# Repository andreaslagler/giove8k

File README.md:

# giove8k
Giove 8k audio synthesizer project

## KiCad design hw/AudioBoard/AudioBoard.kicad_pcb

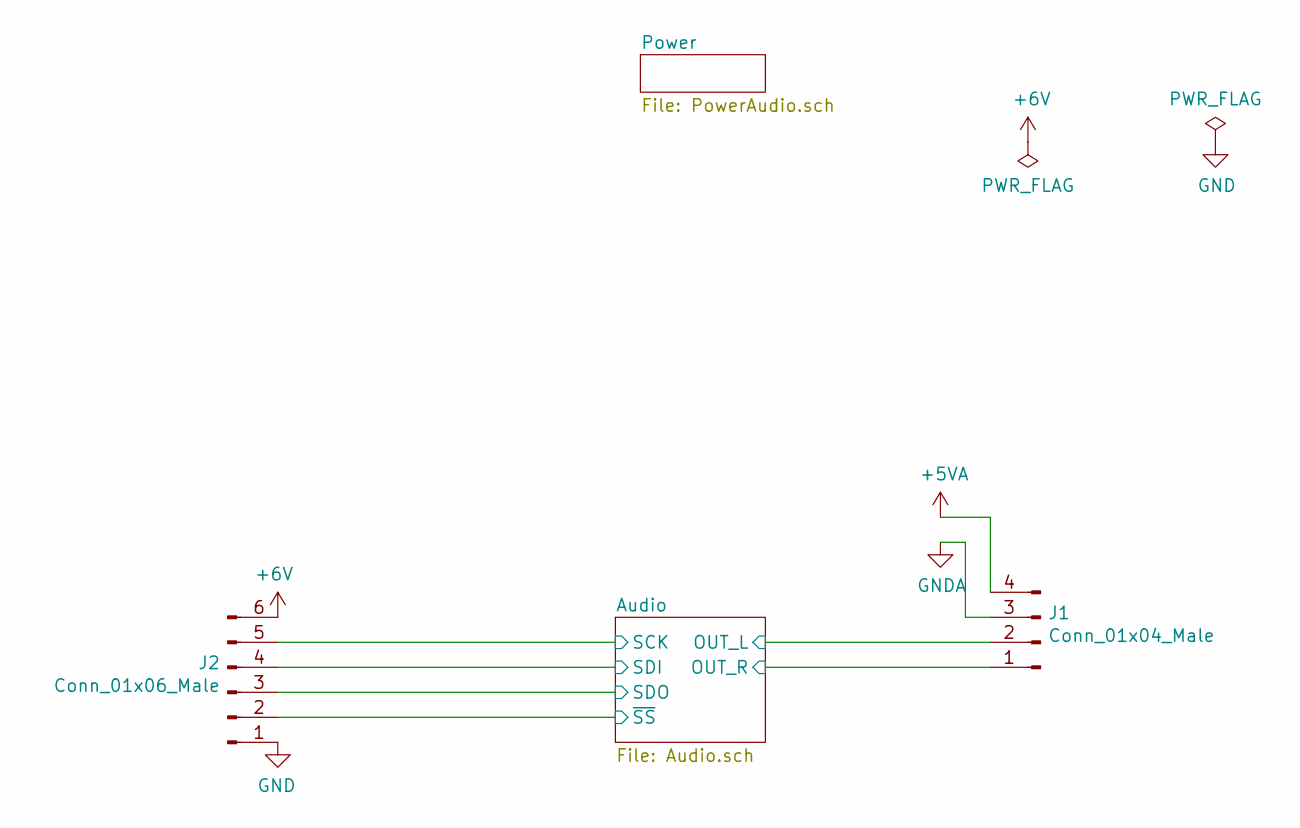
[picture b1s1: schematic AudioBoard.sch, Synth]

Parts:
J1: Conn_01x04_Male; PinHeader_1x04_P2.54mm_Vertical
J2: Conn_01x06_Male; PinHeader_1x06_P2.54mm_Vertical

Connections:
+5VA: J1.4; also elsewhere on the board
+6V: J2.6; also elsewhere on the board
/Audio/OUT_L: J1.2; also elsewhere on the board
/Audio/OUT_R: J1.1; also elsewhere on the board
/Audio/SCK: J2.5; also elsewhere on the board
/Audio/SDI: J2.4; also elsewhere on the board
/Audio/SDO: J2.3; also elsewhere on the board
/Audio/~SS: J2.2; also elsewhere on the board
GND: J1.3, J2.1; also elsewhere on the board

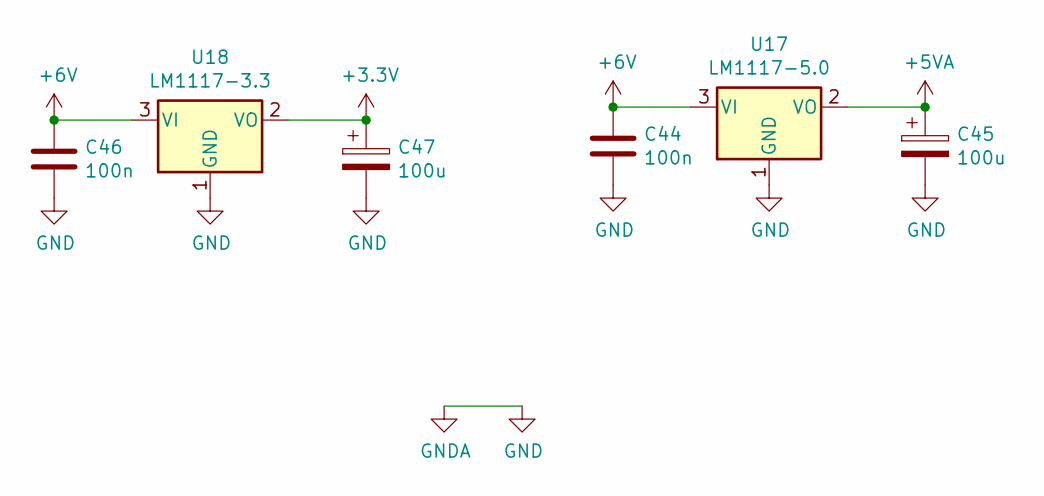
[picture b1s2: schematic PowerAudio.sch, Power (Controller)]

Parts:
C44, C46: 100n; C_Disc_D4.3mm_W1.9mm_P5.00mm
C45, C47: 100u; CP_Radial_D8.0mm_P5.00mm
U17: LM1117-5.0; TO-220F-3_Horizontal_TabDown
U18: LM1117-3.3; TO-220F-3_Horizontal_TabDown

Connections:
+3V3: C47.1, U18.2 (VO); also elsewhere on the board
+5VA: C45.1, U17.2 (VO); also elsewhere on the board
+6V: C44.1, C46.1, U17.3 (VI), U18.3 (VI); also elsewhere on the board
GND: C44.2, C45.2, C46.2, C47.2, U17.1 (GND), U18.1 (GND); also elsewhere on the board

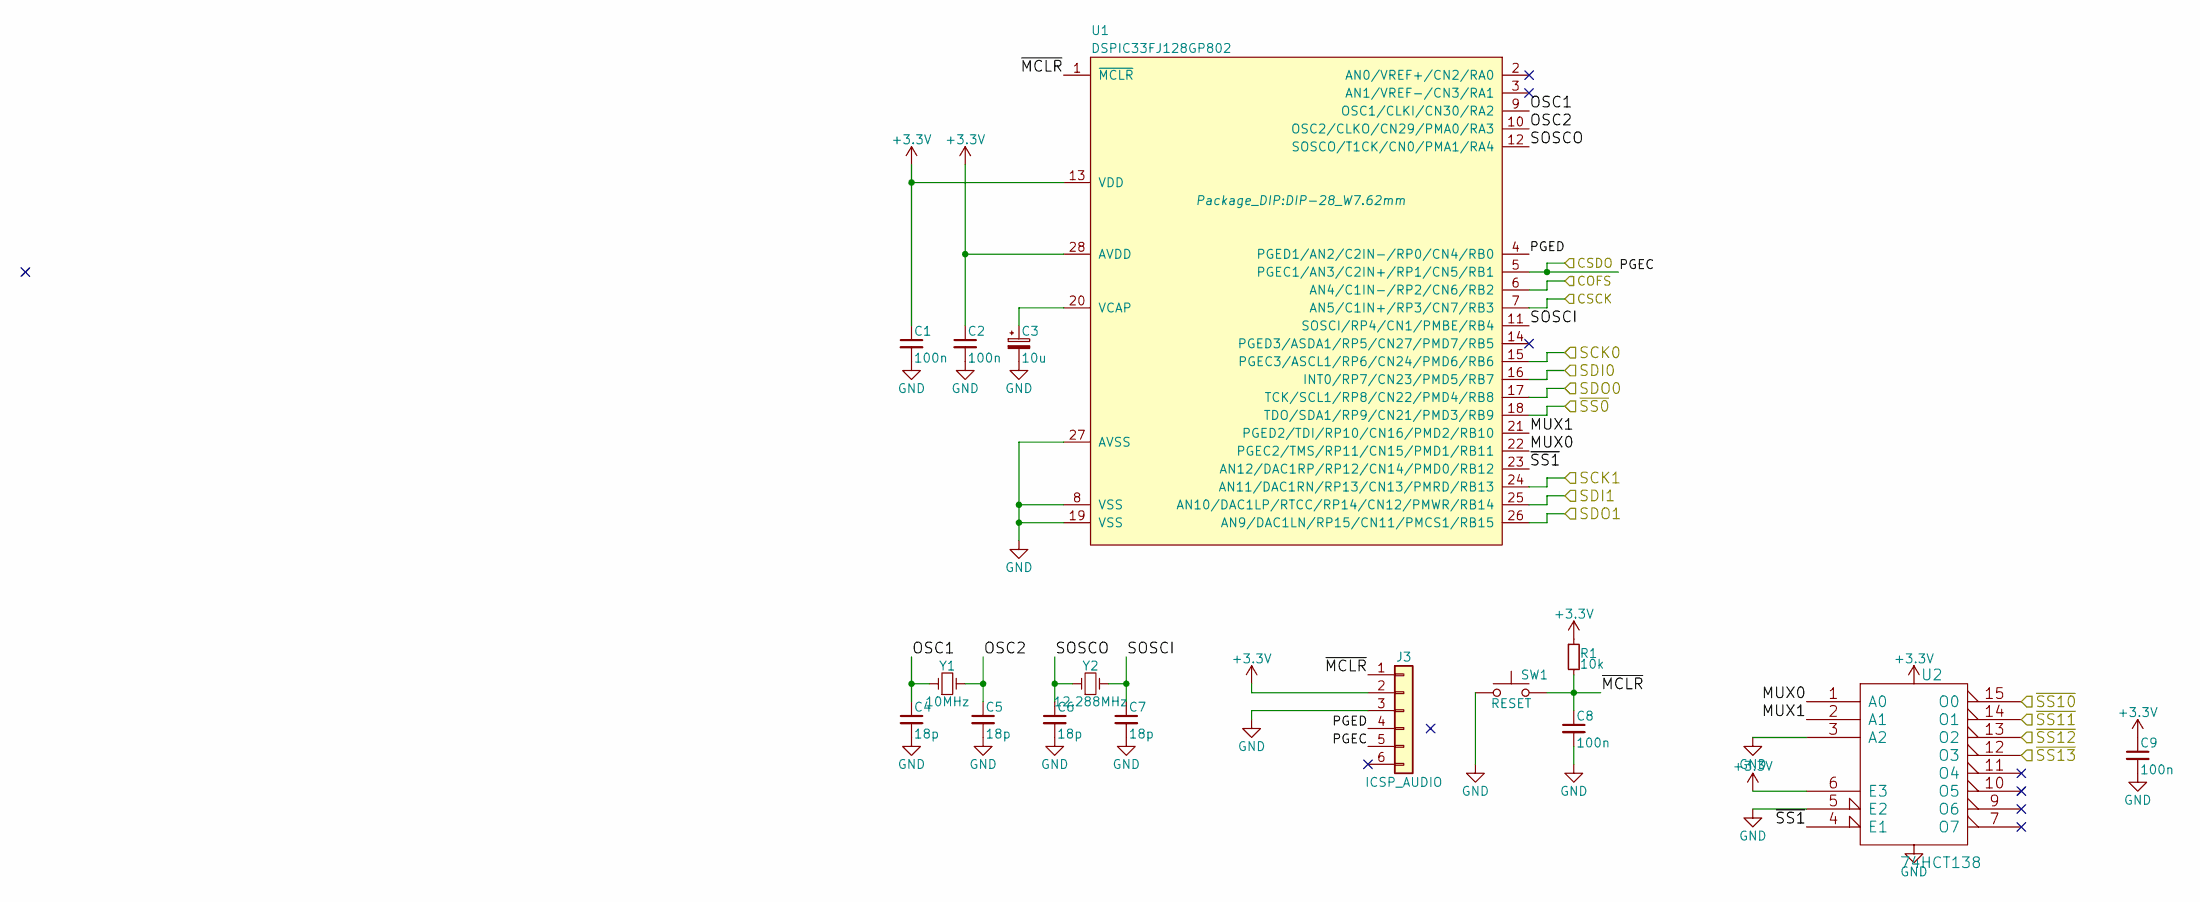
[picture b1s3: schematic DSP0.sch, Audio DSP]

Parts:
C1, C2, C8, C9: 100n; C_Disc_D4.3mm_W1.9mm_P5.00mm
C3: 10u; CP_Radial_D5.0mm_P2.50mm
C4, C5, C6, C7: 18p; C_Disc_D3.0mm_W1.6mm_P2.50mm
J3: ICSP_AUDIO; Molex_KK-254_AE-6410-06A_1x06_P2.54mm_Vertical
R1: 10k; R_Axial_DIN0207_L6.3mm_D2.5mm_P10.16mm_Horizontal
SW1: RESET; SW_PUSH_6mm
U1: DSPIC33FJ128GP802; DIP-28_W7.62mm
U2: 74HCT138; DIP-16_W7.62mm
Y1: 10MHz; Crystal_HC49-U_Vertical
Y2: 12.288MHz; Crystal_HC49-U_Vertical

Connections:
+3V3: C1.1, C2.1, C9.1, J3.2, R1.1, U1.13 (VDD), U1.28 (AVDD), U2.6 (E3), U2.16 (VCC); also elsewhere on the board
/Audio/COFS: U1.6 (AN4/C1IN-/RP2/CN6/RB2); also elsewhere on the board
/Audio/CSDO: J3.5, U1.5 (PGEC1/AN3/C2IN+/RP1/CN5/RB1); also elsewhere on the board
/Audio/CSK: U1.7 (AN5/C1IN+/RP3/CN7/RB3); also elsewhere on the board
/Audio/DSP0/MUX0: U1.22 (PGEC2/TMS/RP11/CN15/PMD1/RB11), U2.1 (A0)
/Audio/DSP0/MUX1: U1.21 (PGED2/TDI/RP10/CN16/PMD2/RB10), U2.2 (A1)
/Audio/DSP0/OSC1: C4.1, U1.9 (OSC1/CLKI/CN30/RA2), Y1.1
/Audio/DSP0/OSC2: C5.1, U1.10 (OSC2/CLKO/CN29/PMA0/RA3), Y1.2
/Audio/DSP0/PGED: J3.4, U1.4 (PGED1/AN2/C2IN-/RP0/CN4/RB0)
/Audio/DSP0/SOSCI: C7.1, U1.11 (SOSCI/RP4/CN1/PMBE/RB4), Y2.2
/Audio/DSP0/SOSCO: C6.1, U1.12 (SOSCO/T1CK/CN0/PMA1/RA4), Y2.1
/Audio/DSP0/~MCLR: C8.1, J3.1, R1.2, SW1.2, U1.1 (~MCLR)
/Audio/DSP0/~SS1: U1.23 (AN12/DAC1RP/RP12/CN14/PMD0/RB12), U2.4 (E1)
/Audio/SCK: U1.15 (PGEC3/ASCL1/RP6/CN24/PMD6/RB6); also elsewhere on the board
/Audio/SCK1: U1.24 (AN11/DAC1RN/RP13/CN13/PMRD/RB13); also elsewhere on the board
/Audio/SDI: U1.16 (INT0/RP7/CN23/PMD5/RB7); also elsewhere on the board
/Audio/SDI1: U1.25 (AN10/DAC1LP/RTCC/RP14/CN12/PMWR/RB14); also elsewhere on the board
/Audio/SDO: U1.17 (TCK/SCL1/RP8/CN22/PMD4/RB8); also elsewhere on the board
/Audio/SDO1: U1.26 (AN9/DAC1LN/RP15/CN11/PMCS1/RB15); also elsewhere on the board
/Audio/~SS: U1.18 (TDO/SDA1/RP9/CN21/PMD3/RB9); also elsewhere on the board
/Audio/~SS0: U2.15 (O0); also elsewhere on the board
/Audio/~SS1: U2.14 (O1); also elsewhere on the board
/Audio/~SS2: U2.13 (O2); also elsewhere on the board
/Audio/~SS3: U2.12 (O3); also elsewhere on the board
GND: C1.2, C2.2, C3.2, C4.2, C5.2, C6.2, C7.2, C8.2, C9.2, J3.3, SW1.1, U1.8 (VSS), U1.19 (VSS), U1.27 (AVSS), U2.3 (A2), U2.5 (E2), U2.8 (GND); also elsewhere on the board
unnamed: C3.1, U1.20 (VCAP)

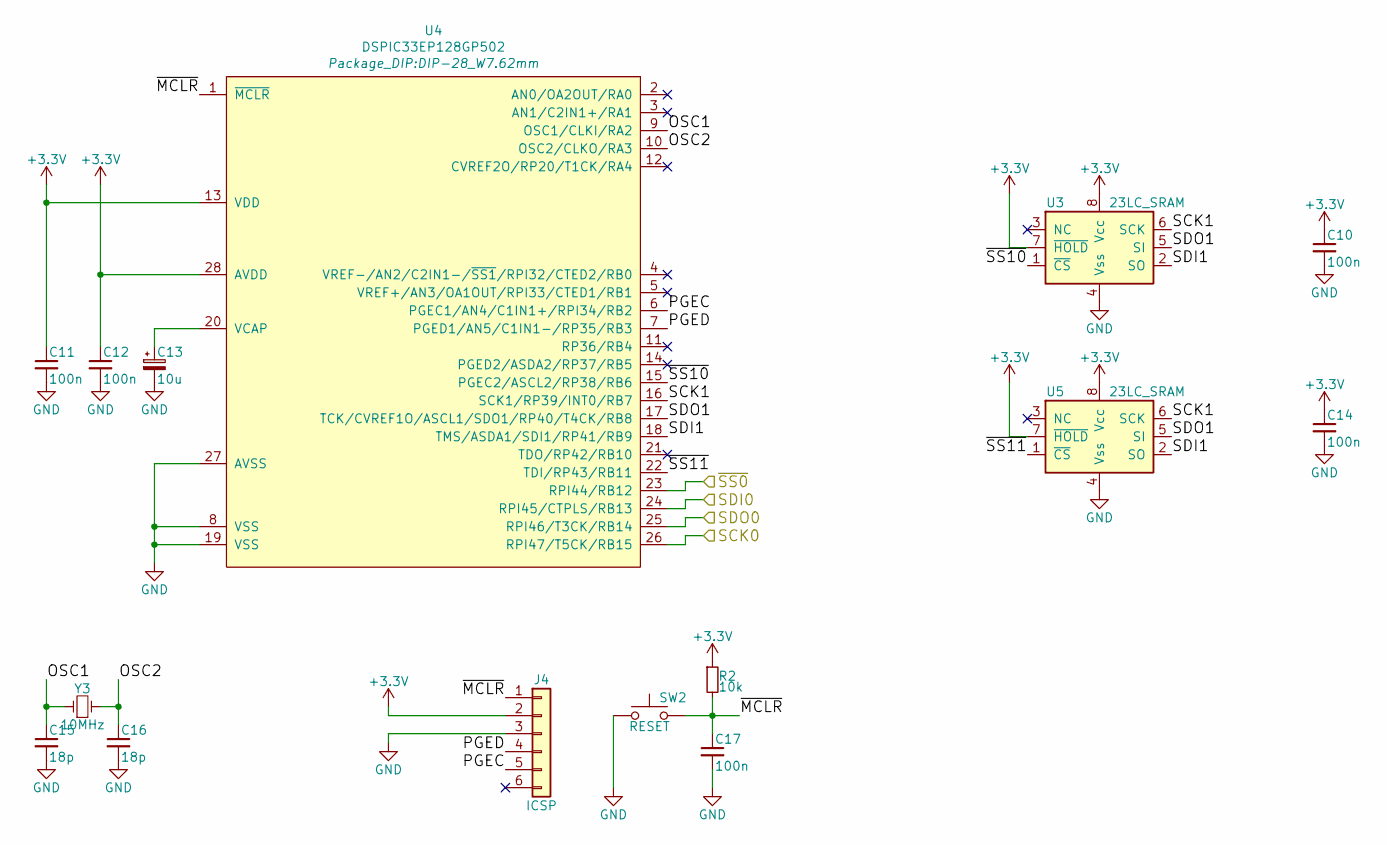
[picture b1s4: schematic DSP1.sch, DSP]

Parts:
C10, C11, C12, C14, C17: 100n; C_Disc_D4.3mm_W1.9mm_P5.00mm
C13: 10u; CP_Radial_D5.0mm_P2.50mm
C15, C16: 18p; C_Disc_D3.0mm_W1.6mm_P2.50mm
J4: ICSP; Molex_KK-254_AE-6410-06A_1x06_P2.54mm_Vertical
R2: 10k; R_Axial_DIN0207_L6.3mm_D2.5mm_P10.16mm_Horizontal
SW2: RESET; SW_PUSH_6mm
U3, U5: 23LC_SRAM; DIP-8_W7.62mm
U4: DSPIC33EP128GP502; DIP-28_W7.62mm
Y3: 10MHz; Crystal_HC49-U_Vertical

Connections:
+3V3: C10.1, C11.1, C12.1, C14.1, J4.2, R2.1, U3.7 (~HOLD), U3.8 (Vcc), U4.13 (VDD), U4.28 (AVDD), U5.7 (~HOLD), U5.8 (Vcc); also elsewhere on the board
/Audio/DSP1/OSC1: C15.1, U4.9 (OSC1/CLKI/RA2), Y3.1
/Audio/DSP1/OSC2: C16.1, U4.10 (OSC2/CLKO/RA3), Y3.2
/Audio/DSP1/PGEC: J4.5, U4.6 (PGEC1/AN4/C1IN1+/RPI34/RB2)
/Audio/DSP1/PGED: J4.4, U4.7 (PGED1/AN5/C1IN1-/RP35/RB3)
/Audio/DSP1/SCK1: U3.6 (SCK), U4.16 (SCK1/RP39/INT0/RB7), U5.6 (SCK)
/Audio/DSP1/SDI1: U3.2 (SO), U4.18 (TMS/ASDA1/SDI1/RP41/RB9), U5.2 (SO)
/Audio/DSP1/SDO1: U3.5 (SI), U4.17 (TCK/CVREF1O/ASCL1/SDO1/RP40/T4CK/RB8), U5.5 (SI)
/Audio/DSP1/~MCLR: C17.1, J4.1, R2.2, SW2.2, U4.1 (~MCLR)
/Audio/DSP1/~SS10: U3.1 (~CS), U4.15 (PGEC2/ASCL2/RP38/RB6)
/Audio/DSP1/~SS11: U4.22 (TDI/RP43/RB11), U5.1 (~CS)
/Audio/SCK1: U4.26 (RPI47/T5CK/RB15); also elsewhere on the board
/Audio/SDI1: U4.25 (RPI46/T3CK/RB14); also elsewhere on the board
/Audio/SDO1: U4.24 (RPI45/CTPLS/RB13); also elsewhere on the board
/Audio/~SS0: U4.23 (RPI44/RB12); also elsewhere on the board
GND: C10.2, C11.2, C12.2, C13.2, C14.2, C15.2, C16.2, C17.2, J4.3, SW2.1, U3.4 (Vss), U4.8 (VSS), U4.19 (VSS), U4.27 (AVSS), U5.4 (Vss); also elsewhere on the board
unnamed: C13.1, U4.20 (VCAP)

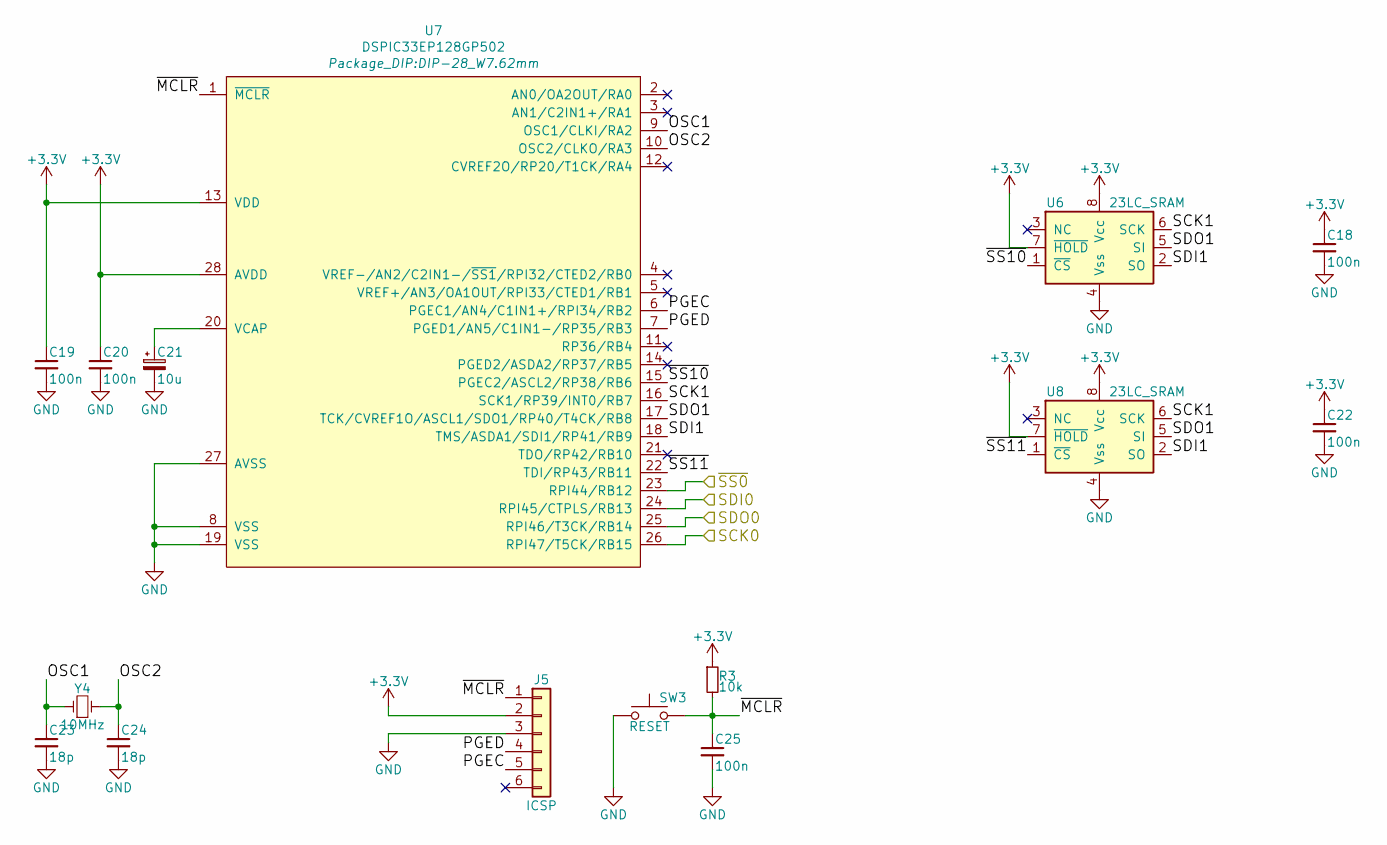
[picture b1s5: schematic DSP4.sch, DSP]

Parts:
C18, C19, C20, C22, C25: 100n; C_Disc_D4.3mm_W1.9mm_P5.00mm
C21: 10u; CP_Radial_D5.0mm_P2.50mm
C23, C24: 18p; C_Disc_D3.0mm_W1.6mm_P2.50mm
J5: ICSP; Molex_KK-254_AE-6410-06A_1x06_P2.54mm_Vertical
R3: 10k; R_Axial_DIN0207_L6.3mm_D2.5mm_P10.16mm_Horizontal
SW3: RESET; SW_PUSH_6mm
U6, U8: 23LC_SRAM; DIP-8_W7.62mm
U7: DSPIC33EP128GP502; DIP-28_W7.62mm
Y4: 10MHz; Crystal_HC49-U_Vertical

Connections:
+3V3: C18.1, C19.1, C20.1, C22.1, J5.2, R3.1, U6.7 (~HOLD), U6.8 (Vcc), U7.13 (VDD), U7.28 (AVDD), U8.7 (~HOLD), U8.8 (Vcc); also elsewhere on the board
/Audio/DSP4/OSC1: C23.1, U7.9 (OSC1/CLKI/RA2), Y4.1
/Audio/DSP4/OSC2: C24.1, U7.10 (OSC2/CLKO/RA3), Y4.2
/Audio/DSP4/PGEC: J5.5, U7.6 (PGEC1/AN4/C1IN1+/RPI34/RB2)
/Audio/DSP4/PGED: J5.4, U7.7 (PGED1/AN5/C1IN1-/RP35/RB3)
/Audio/DSP4/SCK1: U6.6 (SCK), U7.16 (SCK1/RP39/INT0/RB7), U8.6 (SCK)
/Audio/DSP4/SDI1: U6.2 (SO), U7.18 (TMS/ASDA1/SDI1/RP41/RB9), U8.2 (SO)
/Audio/DSP4/SDO1: U6.5 (SI), U7.17 (TCK/CVREF1O/ASCL1/SDO1/RP40/T4CK/RB8), U8.5 (SI)
/Audio/DSP4/~MCLR: C25.1, J5.1, R3.2, SW3.2, U7.1 (~MCLR)
/Audio/DSP4/~SS10: U6.1 (~CS), U7.15 (PGEC2/ASCL2/RP38/RB6)
/Audio/DSP4/~SS11: U7.22 (TDI/RP43/RB11), U8.1 (~CS)
/Audio/SCK1: U7.26 (RPI47/T5CK/RB15); also elsewhere on the board
/Audio/SDI1: U7.25 (RPI46/T3CK/RB14); also elsewhere on the board
/Audio/SDO1: U7.24 (RPI45/CTPLS/RB13); also elsewhere on the board
/Audio/~SS3: U7.23 (RPI44/RB12); also elsewhere on the board
GND: C18.2, C19.2, C20.2, C21.2, C22.2, C23.2, C24.2, C25.2, J5.3, SW3.1, U6.4 (Vss), U7.8 (VSS), U7.19 (VSS), U7.27 (AVSS), U8.4 (Vss); also elsewhere on the board
unnamed: C21.1, U7.20 (VCAP)

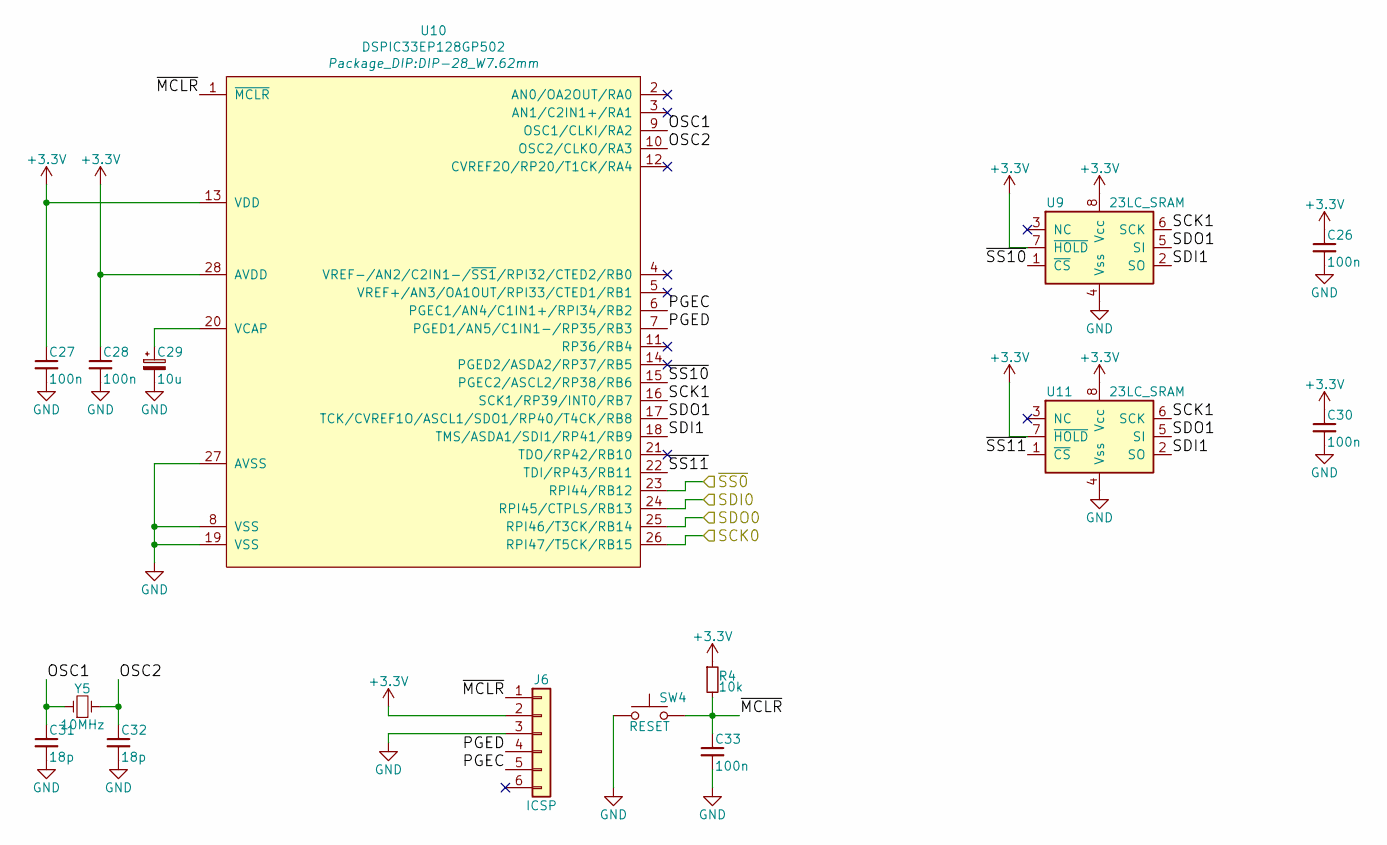
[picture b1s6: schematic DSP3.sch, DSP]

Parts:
C26, C27, C28, C30, C33: 100n; C_Disc_D4.3mm_W1.9mm_P5.00mm
C29: 10u; CP_Radial_D5.0mm_P2.50mm
C31, C32: 18p; C_Disc_D3.0mm_W1.6mm_P2.50mm
J6: ICSP; Molex_KK-254_AE-6410-06A_1x06_P2.54mm_Vertical
R4: 10k; R_Axial_DIN0207_L6.3mm_D2.5mm_P10.16mm_Horizontal
SW4: RESET; SW_PUSH_6mm
U9, U11: 23LC_SRAM; DIP-8_W7.62mm
U10: DSPIC33EP128GP502; DIP-28_W7.62mm
Y5: 10MHz; Crystal_HC49-U_Vertical

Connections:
+3V3: C26.1, C27.1, C28.1, C30.1, J6.2, R4.1, U9.7 (~HOLD), U9.8 (Vcc), U10.13 (VDD), U10.28 (AVDD), U11.7 (~HOLD), U11.8 (Vcc); also elsewhere on the board
/Audio/DSP3/OSC1: C31.1, U10.9 (OSC1/CLKI/RA2), Y5.1
/Audio/DSP3/OSC2: C32.1, U10.10 (OSC2/CLKO/RA3), Y5.2
/Audio/DSP3/PGEC: J6.5, U10.6 (PGEC1/AN4/C1IN1+/RPI34/RB2)
/Audio/DSP3/PGED: J6.4, U10.7 (PGED1/AN5/C1IN1-/RP35/RB3)
/Audio/DSP3/SCK1: U9.6 (SCK), U10.16 (SCK1/RP39/INT0/RB7), U11.6 (SCK)
/Audio/DSP3/SDI1: U9.2 (SO), U10.18 (TMS/ASDA1/SDI1/RP41/RB9), U11.2 (SO)
/Audio/DSP3/SDO1: U9.5 (SI), U10.17 (TCK/CVREF1O/ASCL1/SDO1/RP40/T4CK/RB8), U11.5 (SI)
/Audio/DSP3/~MCLR: C33.1, J6.1, R4.2, SW4.2, U10.1 (~MCLR)
/Audio/DSP3/~SS10: U9.1 (~CS), U10.15 (PGEC2/ASCL2/RP38/RB6)
/Audio/DSP3/~SS11: U10.22 (TDI/RP43/RB11), U11.1 (~CS)
/Audio/SCK1: U10.26 (RPI47/T5CK/RB15); also elsewhere on the board
/Audio/SDI1: U10.25 (RPI46/T3CK/RB14); also elsewhere on the board
/Audio/SDO1: U10.24 (RPI45/CTPLS/RB13); also elsewhere on the board
/Audio/~SS2: U10.23 (RPI44/RB12); also elsewhere on the board
GND: C26.2, C27.2, C28.2, C29.2, C30.2, C31.2, C32.2, C33.2, J6.3, SW4.1, U9.4 (Vss), U10.8 (VSS), U10.19 (VSS), U10.27 (AVSS), U11.4 (Vss); also elsewhere on the board
unnamed: C29.1, U10.20 (VCAP)

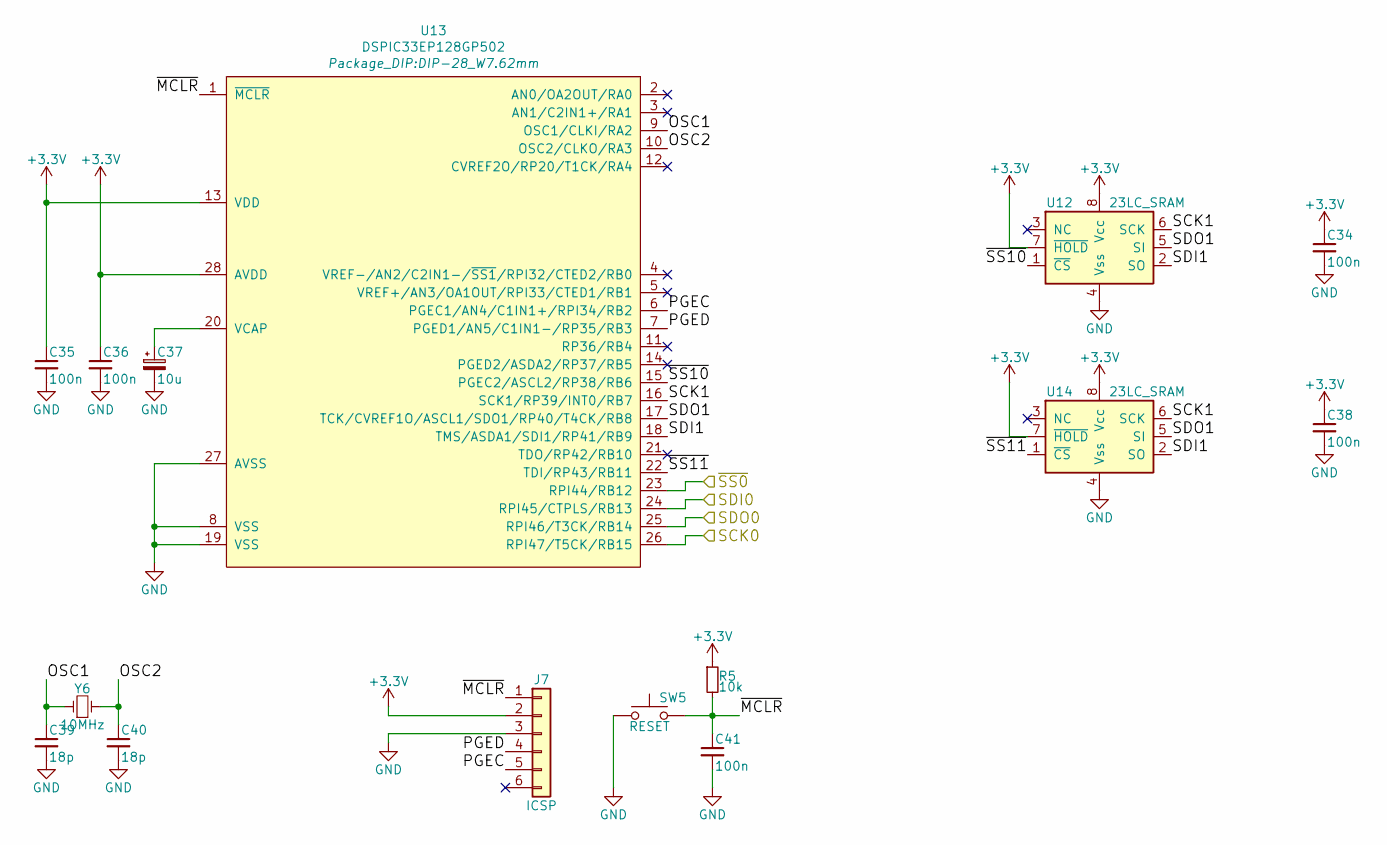
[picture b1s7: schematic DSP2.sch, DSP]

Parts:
C34, C35, C36, C38, C41: 100n; C_Disc_D4.3mm_W1.9mm_P5.00mm
C37: 10u; CP_Radial_D5.0mm_P2.50mm
C39, C40: 18p; C_Disc_D3.0mm_W1.6mm_P2.50mm
J7: ICSP; Molex_KK-254_AE-6410-06A_1x06_P2.54mm_Vertical
R5: 10k; R_Axial_DIN0207_L6.3mm_D2.5mm_P10.16mm_Horizontal
SW5: RESET; SW_PUSH_6mm
U12, U14: 23LC_SRAM; DIP-8_W7.62mm
U13: DSPIC33EP128GP502; DIP-28_W7.62mm
Y6: 10MHz; Crystal_HC49-U_Vertical

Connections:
+3V3: C34.1, C35.1, C36.1, C38.1, J7.2, R5.1, U12.7 (~HOLD), U12.8 (Vcc), U13.13 (VDD), U13.28 (AVDD), U14.7 (~HOLD), U14.8 (Vcc); also elsewhere on the board
/Audio/DSP2/OSC1: C39.1, U13.9 (OSC1/CLKI/RA2), Y6.1
/Audio/DSP2/OSC2: C40.1, U13.10 (OSC2/CLKO/RA3), Y6.2
/Audio/DSP2/PGEC: J7.5, U13.6 (PGEC1/AN4/C1IN1+/RPI34/RB2)
/Audio/DSP2/PGED: J7.4, U13.7 (PGED1/AN5/C1IN1-/RP35/RB3)
/Audio/DSP2/SCK1: U12.6 (SCK), U13.16 (SCK1/RP39/INT0/RB7), U14.6 (SCK)
/Audio/DSP2/SDI1: U12.2 (SO), U13.18 (TMS/ASDA1/SDI1/RP41/RB9), U14.2 (SO)
/Audio/DSP2/SDO1: U12.5 (SI), U13.17 (TCK/CVREF1O/ASCL1/SDO1/RP40/T4CK/RB8), U14.5 (SI)
/Audio/DSP2/~MCLR: C41.1, J7.1, R5.2, SW5.2, U13.1 (~MCLR)
/Audio/DSP2/~SS10: U12.1 (~CS), U13.15 (PGEC2/ASCL2/RP38/RB6)
/Audio/DSP2/~SS11: U13.22 (TDI/RP43/RB11), U14.1 (~CS)
/Audio/SCK1: U13.26 (RPI47/T5CK/RB15); also elsewhere on the board
/Audio/SDI1: U13.25 (RPI46/T3CK/RB14); also elsewhere on the board
/Audio/SDO1: U13.24 (RPI45/CTPLS/RB13); also elsewhere on the board
/Audio/~SS1: U13.23 (RPI44/RB12); also elsewhere on the board
GND: C34.2, C35.2, C36.2, C37.2, C38.2, C39.2, C40.2, C41.2, J7.3, SW5.1, U12.4 (Vss), U13.8 (VSS), U13.19 (VSS), U13.27 (AVSS), U14.4 (Vss); also elsewhere on the board
unnamed: C37.1, U13.20 (VCAP)

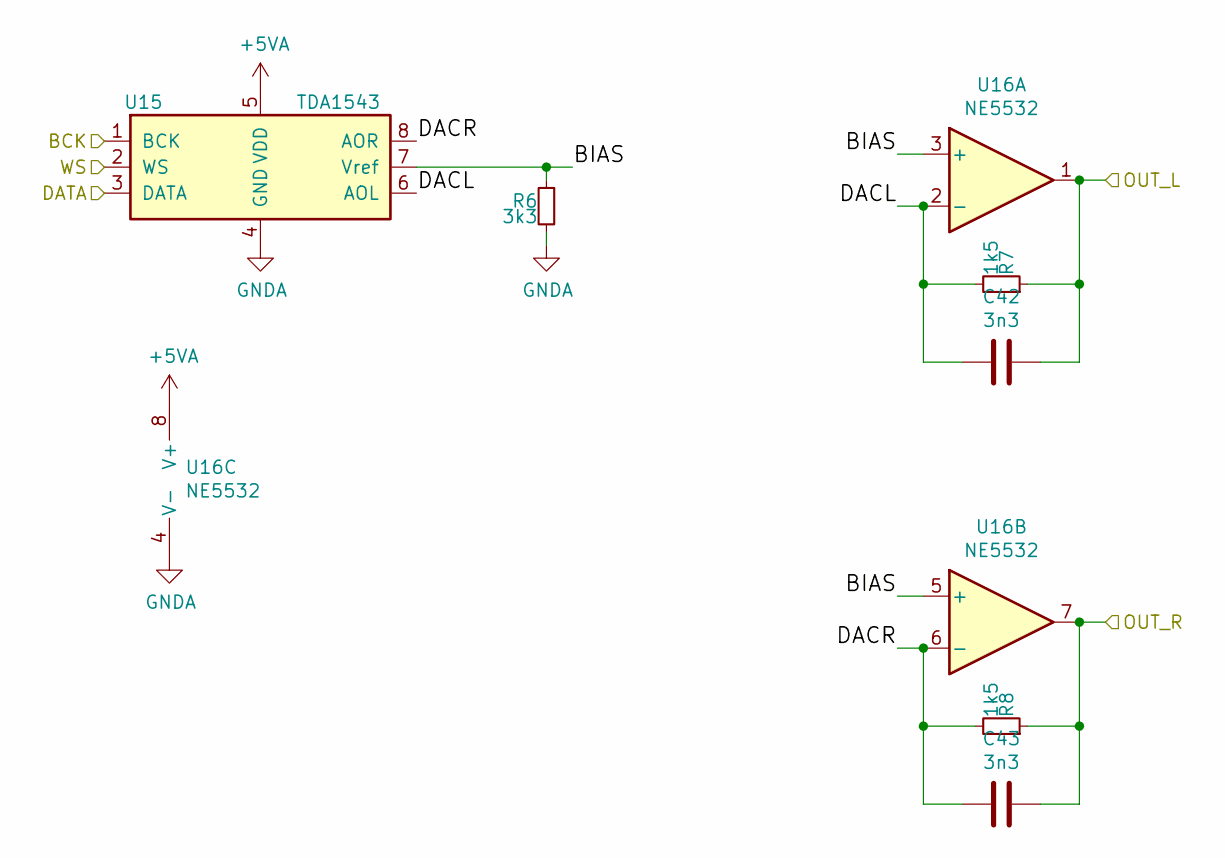
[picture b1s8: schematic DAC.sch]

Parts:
C42, C43: 3n3; C_Disc_D4.3mm_W1.9mm_P5.00mm
R6: 3k3; R_Axial_DIN0207_L6.3mm_D2.5mm_P10.16mm_Horizontal
R7, R8: 1k5; R_Axial_DIN0207_L6.3mm_D2.5mm_P10.16mm_Horizontal
U15: TDA1543; DIP-8_W7.62mm
U16: NE5532; DIP-8_W7.62mm

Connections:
+5VA: U15.5 (VDD), U16.8 (V+); also elsewhere on the board
/Audio/COFS: U15.2 (WS); also elsewhere on the board
/Audio/CSDO: U15.3 (DATA); also elsewhere on the board
/Audio/CSK: U15.1 (BCK); also elsewhere on the board
/Audio/DAC/BIAS: R6.1, U15.7 (Vref), U16.3 (+), U16.5 (+)
/Audio/DAC/DACL: C42.2, R7.2, U15.6 (AOL), U16.2 (-)
/Audio/DAC/DACR: C43.2, R8.2, U15.8 (AOR), U16.6 (-)
/Audio/OUT_L: C42.1, R7.1, U16.1; also elsewhere on the board
/Audio/OUT_R: C43.1, R8.1, U16.7; also elsewhere on the board
GND: R6.2, U15.4 (GND), U16.4 (V-); also elsewhere on the board

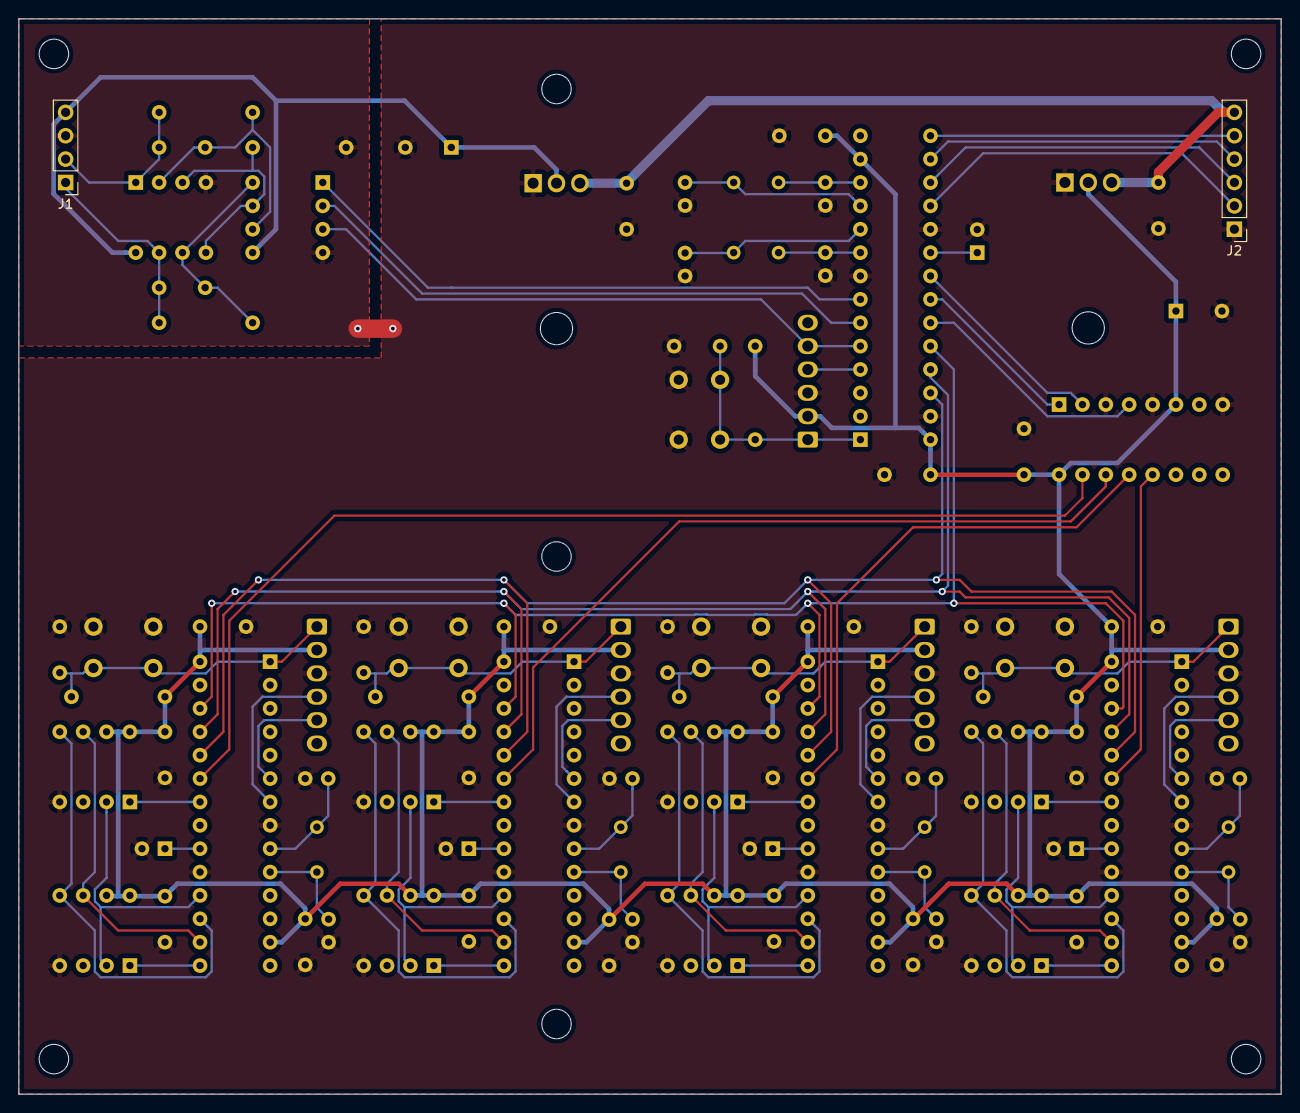
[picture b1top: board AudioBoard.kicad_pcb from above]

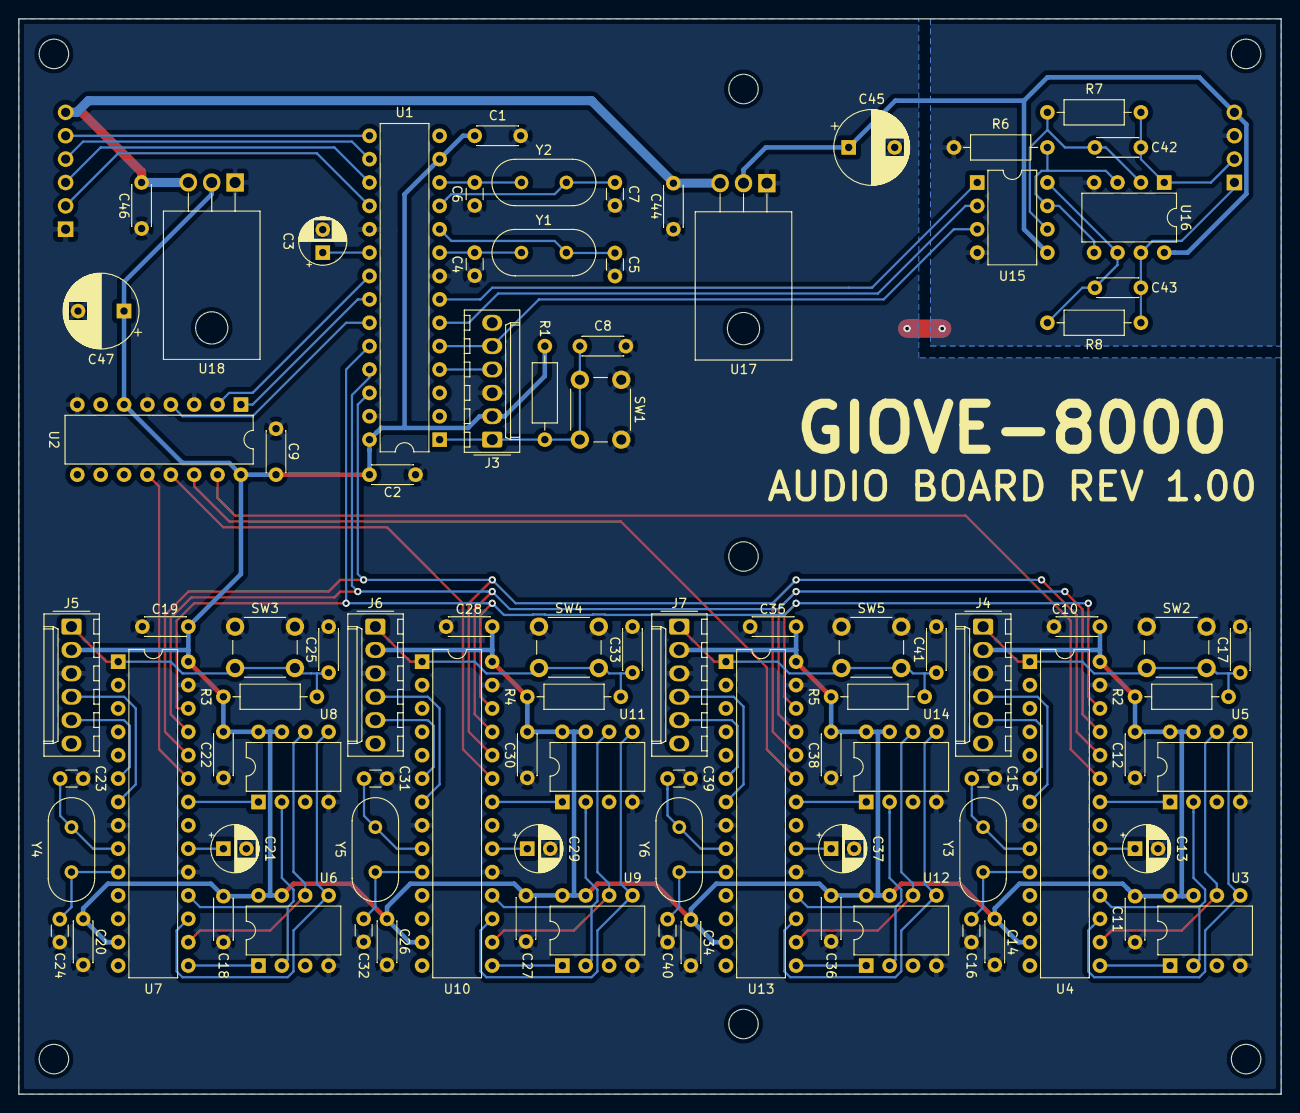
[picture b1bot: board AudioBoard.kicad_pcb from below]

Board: 2 copper layers, 137.2 x 116.8 mm, 91 parts (89 on the bottom side), 77 nets.

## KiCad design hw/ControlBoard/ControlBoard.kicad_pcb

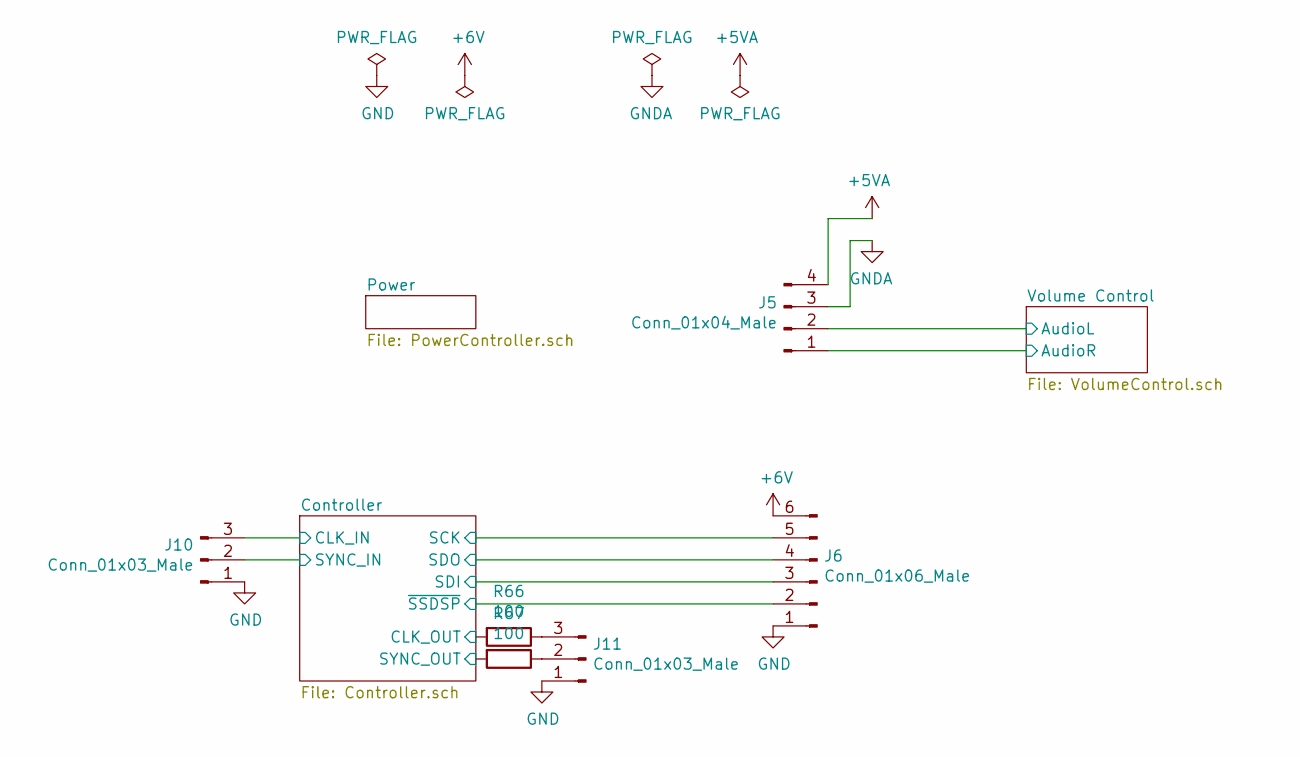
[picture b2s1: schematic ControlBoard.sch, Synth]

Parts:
J5: Conn_01x04_Male; PinHeader_1x04_P2.54mm_Vertical
J6: Conn_01x06_Male; PinHeader_1x06_P2.54mm_Vertical
J10, J11: Conn_01x03_Male; Molex_KK-254_AE-6410-03A_1x03_P2.54mm_Vertical
R66, R67: 100; R_Axial_DIN0207_L6.3mm_D2.5mm_P10.16mm_Horizontal

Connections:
+5VA: J5.4; also elsewhere on the board
+6V: J6.6; also elsewhere on the board
/Controller/CLK_IN: J10.3; also elsewhere on the board
/Controller/CLK_OUT: R66.2; also elsewhere on the board
/Controller/SCK: J6.5; also elsewhere on the board
/Controller/SDI: J6.3; also elsewhere on the board
/Controller/SDO: J6.4; also elsewhere on the board
/Controller/SYNC_IN: J10.2; also elsewhere on the board
/Controller/SYNC_OUT: R67.2; also elsewhere on the board
/Controller/~SSDSP: J6.2; also elsewhere on the board
/Volume Control/AudioL: J5.2; also elsewhere on the board
/Volume Control/AudioR: J5.1; also elsewhere on the board
GND: J6.1, J10.1, J11.1; also elsewhere on the board
GNDA: J5.3; also elsewhere on the board
unnamed: J11.2, R67.1
unnamed: J11.3, R66.1

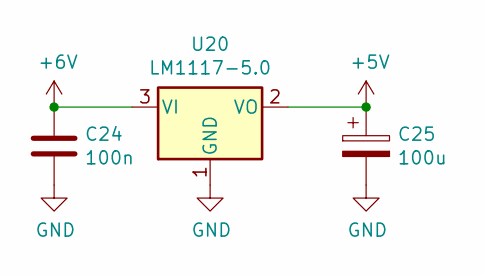
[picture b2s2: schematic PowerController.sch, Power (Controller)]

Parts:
C24: 100n; C_Disc_D5.0mm_W2.5mm_P5.00mm
C25: 100u; CP_Radial_D8.0mm_P5.00mm
U20: LM1117-5.0; TO-220-3_Vertical

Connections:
+5V: C25.1, U20.2 (VO); also elsewhere on the board
+6V: C24.1, U20.3 (VI); also elsewhere on the board
GND: C24.2, C25.2, U20.1 (GND); also elsewhere on the board

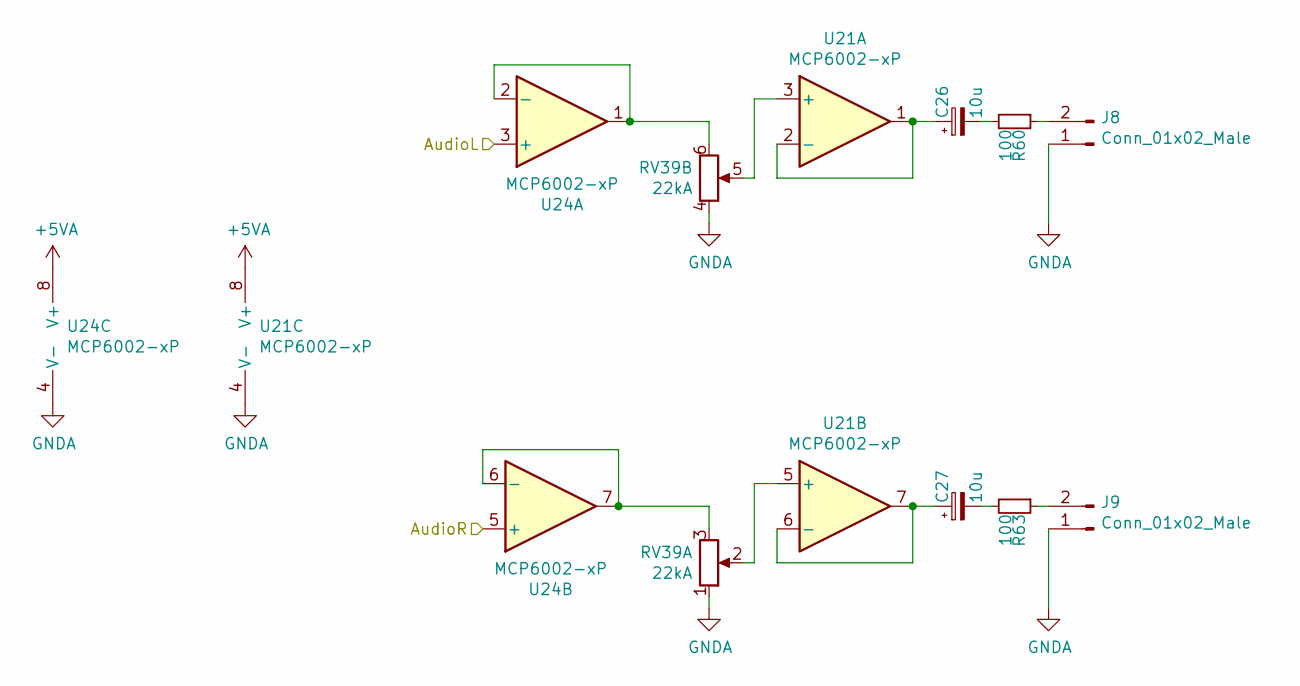
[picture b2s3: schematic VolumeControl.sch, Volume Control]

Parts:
C26, C27: 10u; CP_Radial_D5.0mm_P2.50mm
J8, J9: Conn_01x02_Male; Molex_KK-254_AE-6410-02A_1x02_P2.54mm_Vertical
R60, R63: 100; R_Axial_DIN0207_L6.3mm_D2.5mm_P10.16mm_Horizontal
RV39: 22kA; Potentiometer_Alpha_RD902F-40-00D_Dual_Vertical_CircularHol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
U21, U24: MCP6002-xP; DIP-8_W7.62mm

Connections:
+5VA: U21.8 (V+), U24.8 (V+); also elsewhere on the board
/Volume Control/AudioL: U24.3 (+); also elsewhere on the board
/Volume Control/AudioR: U24.5 (+); also elsewhere on the board
GNDA: J8.1, J9.1, RV39.1, RV39.4, U21.4 (V-), U24.4 (V-); also elsewhere on the board
unnamed: C26.1, U21.1, U21.2 (-)
unnamed: C26.2, R60.2
unnamed: C27.1, U21.6 (-), U21.7
unnamed: C27.2, R63.2
unnamed: J8.2, R60.1
unnamed: J9.2, R63.1
unnamed: RV39.2, U21.5 (+)
unnamed: RV39.3, U24.6 (-), U24.7
unnamed: RV39.5, U21.3 (+)
unnamed: RV39.6, U24.1, U24.2 (-)

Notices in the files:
sw/WaveGen.X/main.c:
Copyright (C) 2021 Andreas Lagler
This program is free software: you can redistribute it and/or modify
it under the terms of the GNU General Public License as published by
the Free Software Foundation, either version 3 of the License, or
(at your option) any later version.
